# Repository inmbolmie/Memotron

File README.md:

# Memotron 256

__Retro-inspired DIY 256KB memory expansion for the Amstrad CPC 464 computers__

## Introduction

This is a clone of an original 1986 DK'Tronics 64/256KB memory expansion that is plugged into the expansion port of the CPC 464 computer. It is made as period-correct as possible regarding components and mechanical design, and at the same time it is possible to easily manufacture it at home as it uses only through-hole components.

If you have looked for these expansions you will know that they are quite hard to find and relatively expensive, especially for the 256KB variant.

If you like it or if you have any questions, you can drop me a message to my email __inmbolmie [AT] gmail [DOT] com__

## Design

The Memotron 256 has more or less the same board layout as the DK'Tronics 64/256KB memory expansion. I have changed the layout of the edge connectors though to make it easier to manufacture at the expense of taking a little more space on the desk, as the connectors are installed on the plane of the PCB and not perpendicular to it like in the original expansion.

So in the original expansion the PCB is in vertical position when plugged into the computer, while on the Memotron the PCB is placed horizontally. It will take more space but the designed 3D-printed case will provide adequate support for it.

Here you can see the Memotron next to the original DK'Tronics expansion PCB:

The board has an expansion edge connector like the original version where you can plug additional hardware, like disk drives, more expansions, etc.

## Compatibility

The expansion will operate exactly the same as the original. It has been tested on a CPC 464 computer adding to the expansion a Zaxxon DDI-1 disk controller and drive emulator

This is a screenshot of how the extra memory is seen on the Amstrad Diagnostics V1.3A application https://github.com/llopis/amstrad-diagnostics

It has been successfully used with games designed to make use of the 128KB of the CPC 6128, as well as some games and apps that will make use of the full 256KB (like Chibiakumas episode 2 https://www.chibiakumas.com/ep2/), and on CP/M 2.2

The expansion when plugged into a CPC 464 will have its memory mapped to banks 00-03 and you will have a total of 320KB of memory available.

The expansion can be configured with the jumpers also as a 64KB expansion, but this doesn't make much sense as the required memory ICs will cost more or less the same for getting 64KB or 256KB.

The Memotron can be used as a silicon disk connecting the jumper labelled as "Silicon disk enable". What this jumper really does is to change the RAM bank mappings from 00-03 to 04-07 so that you can plug two expansions at the same time for a total of 512KB of extra memory. Like in the original to really use it as a silicon disk you will need external roms not included.

Of course there are a lot of other memory expansions for the CPC made with modern components and going up to 4MB in size, that will be more convenient to use than this one. The point of this project though is being as period-correct as possible (no FPGA rubbish and so ;-) and to be possible to manufacture it at home.

## CPC 6128

Regarding the CPC 6128, the expansion seem to work on BASIC and games (Chibiakumas 2 will work and use the whole 256KB), but doesn't work on CP/M plus, so it is not really 100% compatible with the 6128. DK'Tronics had back in the day a specific version of these expansions for the 6128.

The expansion case feet are removable so contrary to the original one the Memotron will physically fit the 6128 without raising the computer.

When plugged into a CPC 6128, the expansion will have its memory mapped to banks 01-04 and you will have a total of 384KB of memory available.

## Board

There is not much to say about the board as it is the same general layout as the original. I provide all the Kicad designs for the project, as well as a ZIP file containing the gerbers needed to manufacture the board on your favourite online fabricator.

When using the services of a PCB fabricator I recommend manufacturing them with gold fingers and chamfered edge connector. Although that will increase the PCB cost substantially, it will improve the quality of the connection and make it more reliable even than that of the original expansions.

To configure the board as 256KB you will place two jumpers HORIZONTALLY as seen on the picture connecting JP1 to JP2. To configure the board as 64KB you will place only the JP2 jumper VERTICALLY.

### BOM

* One 2x25-pin 2,54mm pitch 90-degree bent edge connector
* 2x74LS157
* 1x74LS74
* 1x74LS153
* 1x74LS174
* 1x74LS27
* 1x74LS11
* 1xPAL16L8 or compatible
* 8xD41256C-15 256Kbit RAM or equivalent
* Pins and jumpers
* 3x680 ohm resistors
* 1x1N4148 diode
* 2xBF241 NPN transistors or equivalent
* 16x100nF ceramic capacitors
* 1x82nF ceramic capacitor (the value is critical and this and/or the value of the R3 resistor may need adjustment)
* Optionally, sockets for all the ICs. The original expansion only had sockets for the eight RAM chips

## 3D-printed enclosure

I provide the STL files for the 3D-printed enclosure that can be printed in four parts (top, bottom, feet and panel). There is a version of the top piece with and without the hole for the name plate.

You will need four M3x12mm and two M3x5mm tapered head screws for assembly.

The case is quite sturdy even printed in PLA and will take typically like 7 hours to print.

### PLD

Regarding the PLD that's on the board, the original expansion uses a vintage PAL16L8 ic that nowadays is pretty deprecated. You can get a vintage unprogrammed piece or use a modern ATF16V8B in its place. It will have to be programmed with a proper PLD programmer from a JED source file. I still don't have my own JED file but you can find one that is compatible with the original memory expansion (tagged as "Datel 64k memory expansion") on this site: https://wiki.pldarchive.co.uk

_"DK'Tronics" and "Datel" are registered trademarks.
All the trademarks are used nominatively to indicate compatibility, and do not indicate affiliation to or endorsement by the trademark owners._

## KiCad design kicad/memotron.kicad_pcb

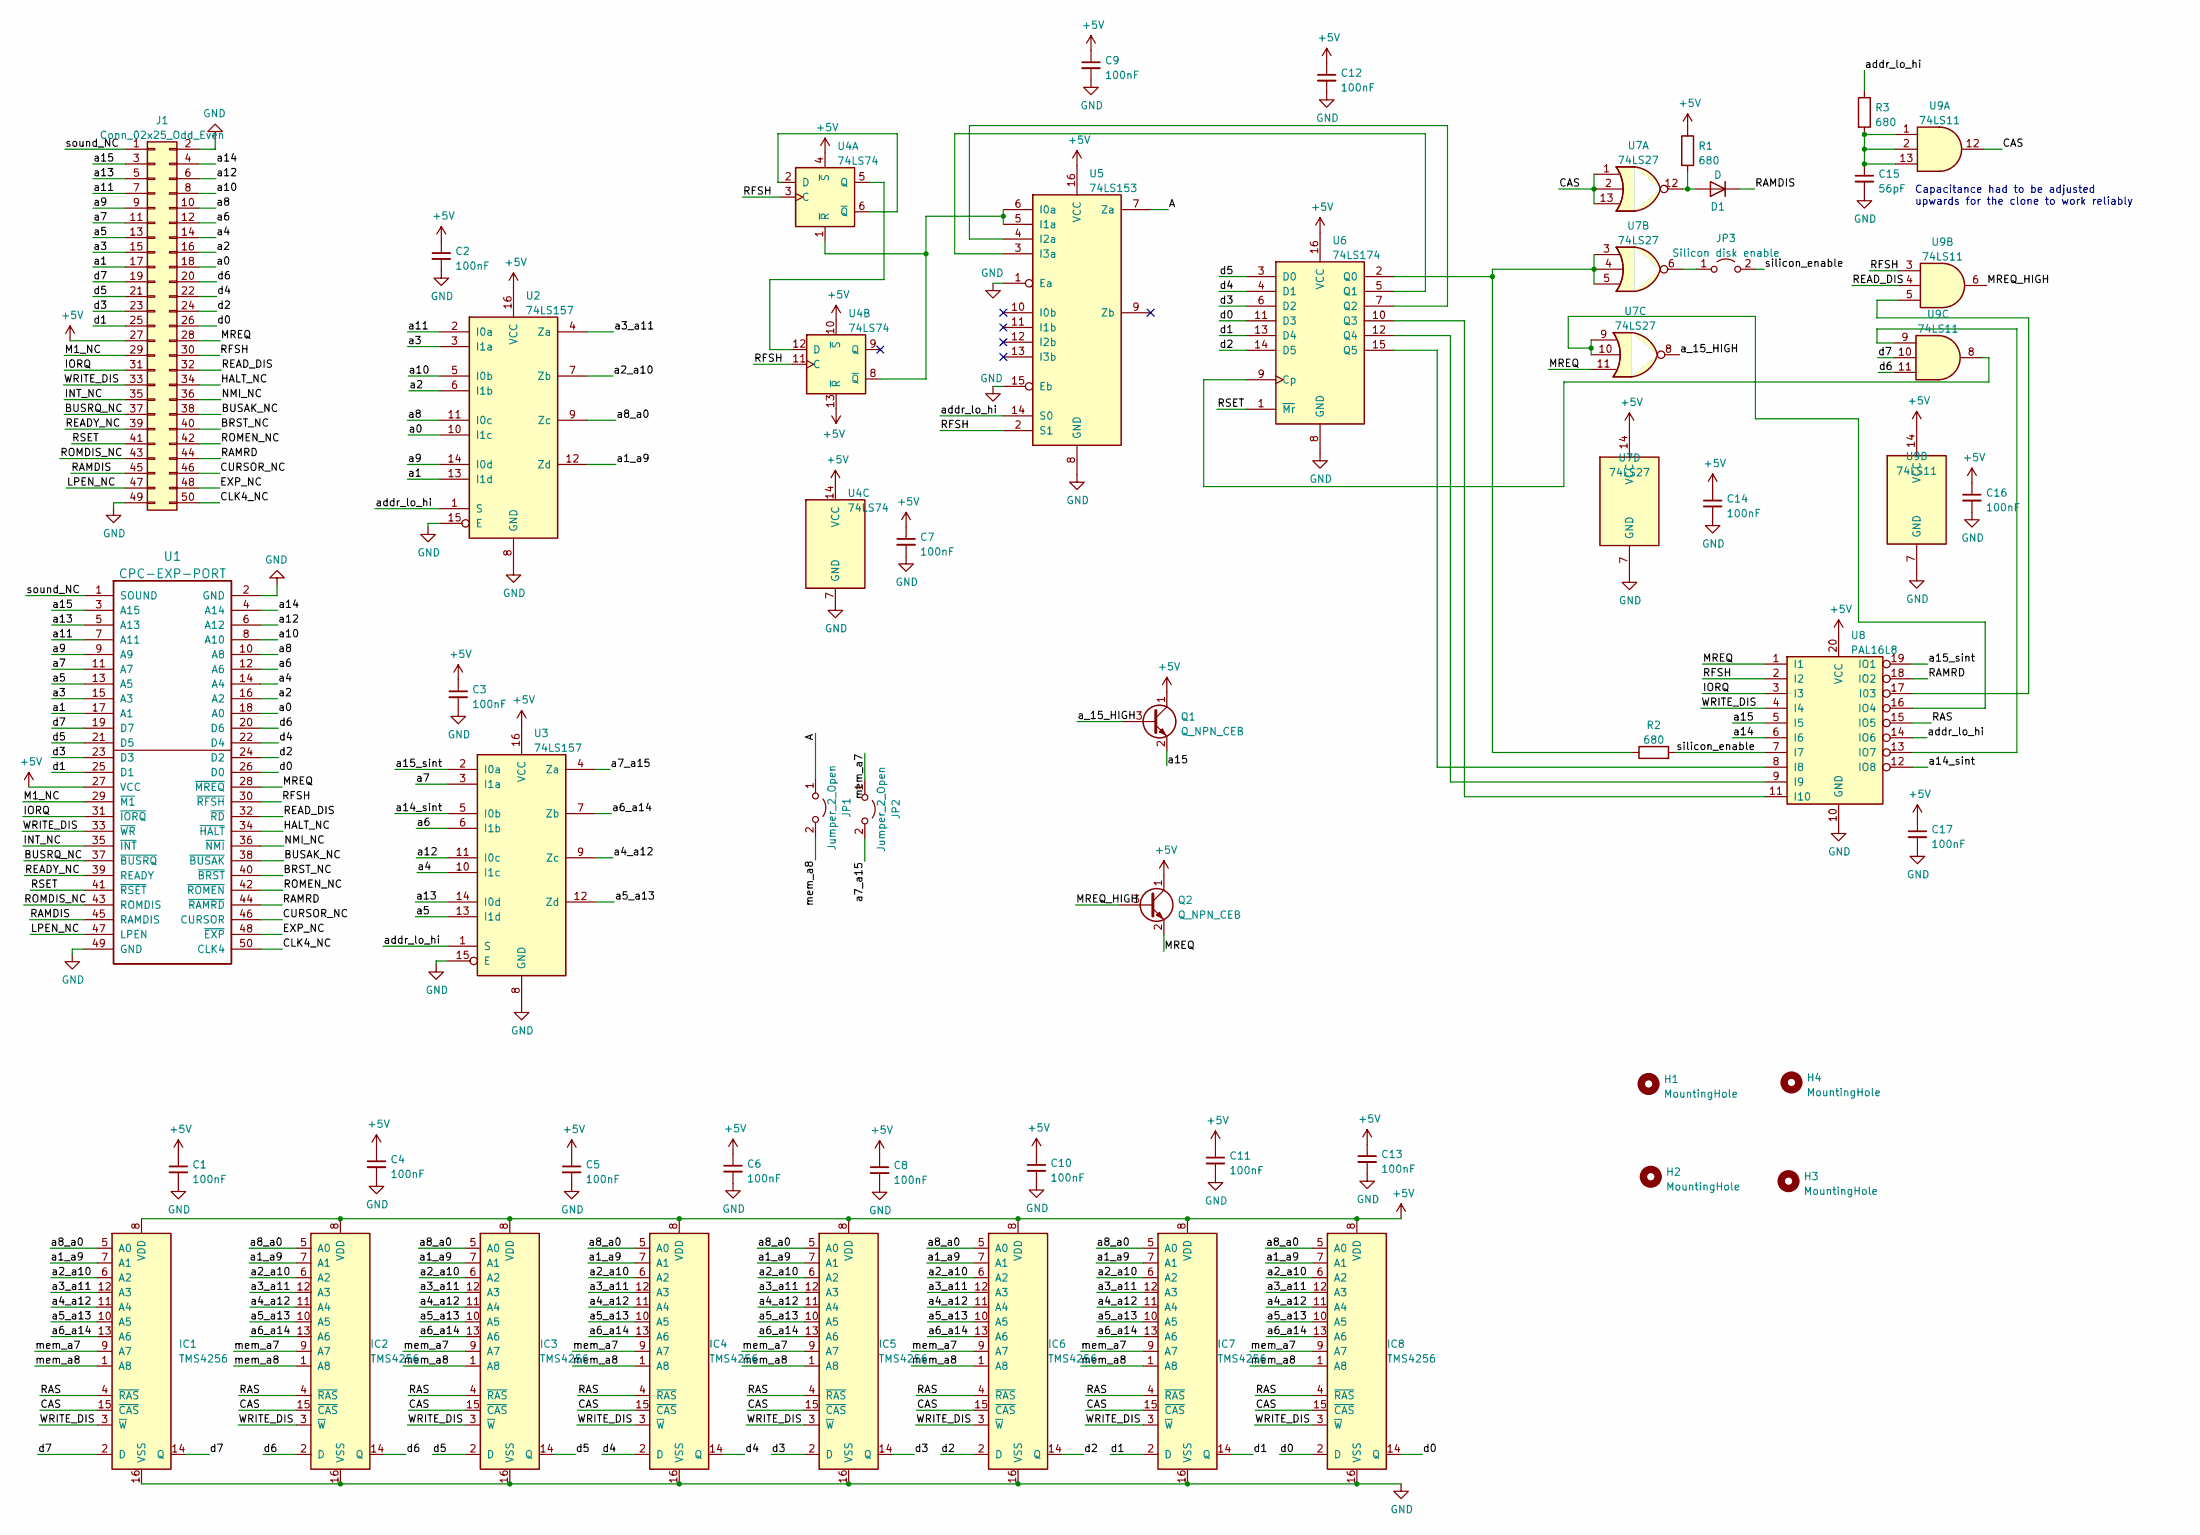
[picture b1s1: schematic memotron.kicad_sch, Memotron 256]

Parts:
C1, C2, C3, C4, C5, C6, C7, C8, C9, C10, C11, C12, C13, C14, C16, C17: 100nF; C_Disc_D6.0mm_W2.5mm_P5.00mm
C15: 56pF; C_Disc_D6.0mm_W2.5mm_P5.00mm
D1: D; D_A-405_P10.16mm_Horizontal
H1, H2, H3, H4: MountingHole; MountingHole_3.2mm_M3_DIN965
IC1, IC2, IC3, IC4, IC5, IC6, IC7, IC8: TMS4256; DIP-16_W7.62mm
J1: Conn_02x25_Odd_Even; PinHeader_2x25_P2.54mm_Horizontal
JP1, JP2: Jumper_2_Open; PinHeader_1x02_P2.54mm_Vertical
JP3: Silicon disk enable; PinHeader_1x02_P2.54mm_Vertical
Q1, Q2: Q_NPN_CEB; TO-92
R1, R2, R3: 680; R_Axial_DIN0309_L9.0mm_D3.2mm_P15.24mm_Horizontal
U1: CPC-EXP-PORT; edge_CPC_25x2
U2, U3: 74LS157; DIP-16_W7.62mm
U4: 74LS74; DIP-14_W7.62mm
U5: 74LS153; DIP-16_W7.62mm
U6: 74LS174; DIP-16_W7.62mm
U7: 74LS27; DIP-14_W7.62mm
U8: PAL16L8; DIP-20_W7.62mm
U9: 74LS11; DIP-14_W7.62mm

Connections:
+5V: C1.1, C2.1, C3.1, C4.1, C5.1, C6.1, C7.1, C8.1, C9.1, C10.1, C11.1, C12.1, C13.1, C14.1, C16.1, C17.1, IC1.8 (VDD), IC2.8 (VDD), IC3.8 (VDD), IC4.8 (VDD), IC5.8 (VDD), IC6.8 (VDD), IC7.8 (VDD), IC8.8 (VDD), J1.27, Q1.1 (C), Q2.1 (C), R1.1, U1.27 (VCC), U2.16 (VCC), U3.16 (VCC), U4.4 (~S), U4.10 (~S), U4.13 (~R), U4.14 (VCC), U5.16 (VCC), U6.16 (VCC), U7.14 (VCC), U8.20 (VCC), U9.14 (VCC)
/A: JP1.1 (A), U5.7 (Za)
/BRST_NC: J1.40, U1.40 (~BRST)
/BUSAK_NC: J1.38, U1.38 (~BUSAK)
/BUSRQ_NC: J1.37, U1.37 (~BUSRQ)
/CAS: IC1.15 (~CAS), IC2.15 (~CAS), IC3.15 (~CAS), IC4.15 (~CAS), IC5.15 (~CAS), IC6.15 (~CAS), IC7.15 (~CAS), IC8.15 (~CAS), U7.1, U7.2, U7.13, U9.12
/CLK4_NC: J1.50, U1.50 (CLK4)
/CURSOR_NC: J1.46, U1.46 (CURSOR)
/EXP_NC: J1.48, U1.48 (~EXP)
/HALT_NC: J1.34, U1.34 (~HALT)
/INT_NC: J1.35, U1.35 (~INT)
/IORQ: J1.31, U1.31 (~IORQ), U8.3 (I3)
/LPEN_NC: J1.47, U1.47 (LPEN)
/M1_NC: J1.29, U1.29 (~M1)
/MREQ: J1.28, Q2.2 (E), U1.28 (~MREQ), U7.11, U8.1 (I1)
/MREQ_HIGH: Q2.3 (B), U9.6
/NMI_NC: J1.36, U1.36 (~NMI)
/RAMDIS: D1.1 (K), J1.45, U1.45 (RAMDIS)
/RAMRD: J1.44, U1.44 (~RAMRD), U8.18 (IO2)
/RAS: IC1.4 (~RAS), IC2.4 (~RAS), IC3.4 (~RAS), IC4.4 (~RAS), IC5.4 (~RAS), IC6.4 (~RAS), IC7.4 (~RAS), IC8.4 (~RAS), U8.15 (IO5)
/READY_NC: J1.39, U1.39 (READY)
/READ_DIS: J1.32, U1.32 (~RD), U9.4
/RFSH: J1.30, U1.30 (~RFSH), U4.3 (C), U4.11 (C), U5.2 (S1), U8.2 (I2), U9.3
/ROMDIS_NC: J1.43, U1.43 (ROMDIS)
/ROMEN_NC: J1.42, U1.42 (~ROMEN)
/RSET: J1.41, U1.41 (~RSET), U6.1 (~Mr)
/WRITE_DIS: IC1.3 (~W), IC2.3 (~W), IC3.3 (~W), IC4.3 (~W), IC5.3 (~W), IC6.3 (~W), IC7.3 (~W), IC8.3 (~W), J1.33, U1.33 (~WR), U8.4 (I4)
/a0: J1.18, U1.18 (A0), U2.10 (I1c)
/a1: J1.17, U1.17 (A1), U2.13 (I1d)
/a1_a9: IC1.7 (A1), IC2.7 (A1), IC3.7 (A1), IC4.7 (A1), IC5.7 (A1), IC6.7 (A1), IC7.7 (A1), IC8.7 (A1), U2.12 (Zd)
/a2: J1.16, U1.16 (A2), U2.6 (I1b)
/a2_a10: IC1.6 (A2), IC2.6 (A2), IC3.6 (A2), IC4.6 (A2), IC5.6 (A2), IC6.6 (A2), IC7.6 (A2), IC8.6 (A2), U2.7 (Zb)
/a3: J1.15, U1.15 (A3), U2.3 (I1a)
/a3_a11: IC1.12 (A3), IC2.12 (A3), IC3.12 (A3), IC4.12 (A3), IC5.12 (A3), IC6.12 (A3), IC7.12 (A3), IC8.12 (A3), U2.4 (Za)
/a4: J1.14, U1.14 (A4), U3.10 (I1c)
/a4_a12: IC1.11 (A4), IC2.11 (A4), IC3.11 (A4), IC4.11 (A4), IC5.11 (A4), IC6.11 (A4), IC7.11 (A4), IC8.11 (A4), U3.9 (Zc)
/a5: J1.13, U1.13 (A5), U3.13 (I1d)
/a5_a13: IC1.10 (A5), IC2.10 (A5), IC3.10 (A5), IC4.10 (A5), IC5.10 (A5), IC6.10 (A5), IC7.10 (A5), IC8.10 (A5), U3.12 (Zd)
/a6: J1.12, U1.12 (A6), U3.6 (I1b)
/a6_a14: IC1.13 (A6), IC2.13 (A6), IC3.13 (A6), IC4.13 (A6), IC5.13 (A6), IC6.13 (A6), IC7.13 (A6), IC8.13 (A6), U3.7 (Zb)
/a7: J1.11, U1.11 (A7), U3.3 (I1a)
/a7_a15: JP2.2 (B), U3.4 (Za)
/a8: J1.10, U1.10 (A8), U2.11 (I0c)
/a8_a0: IC1.5 (A0), IC2.5 (A0), IC3.5 (A0), IC4.5 (A0), IC5.5 (A0), IC6.5 (A0), IC7.5 (A0), IC8.5 (A0), U2.9 (Zc)
/a9: J1.9, U1.9 (A9), U2.14 (I0d)
/a10: J1.8, U1.8 (A10), U2.5 (I0b)
/a11: J1.7, U1.7 (A11), U2.2 (I0a)
/a12: J1.6, U1.6 (A12), U3.11 (I0c)
/a13: J1.5, U1.5 (A13), U3.14 (I0d)
/a14: J1.4, U1.4 (A14), U8.6 (I6)
/a14_sint: U3.5 (I0b), U8.12 (IO8)
/a15: J1.3, Q1.2 (E), U1.3 (A15), U8.5 (I5)
/a15_sint: U3.2 (I0a), U8.19 (IO1)
/a_15_HIGH: Q1.3 (B), U7.8
/addr_lo_hi: R3.1, U2.1 (S), U3.1 (S), U5.14 (S0), U8.14 (IO6)
/d0: IC8.2 (D), IC8.14 (Q), J1.26, U1.26 (D0), U6.11 (D3)
/d1: IC7.2 (D), IC7.14 (Q), J1.25, U1.25 (D1), U6.13 (D4)
/d2: IC6.2 (D), IC6.14 (Q), J1.24, U1.24 (D2), U6.14 (D5)
/d3: IC5.2 (D), IC5.14 (Q), J1.23, U1.23 (D3), U6.6 (D2)
/d4: IC4.2 (D), IC4.14 (Q), J1.22, U1.22 (D4), U6.4 (D1)
/d5: IC3.2 (D), IC3.14 (Q), J1.21, U1.21 (D5), U6.3 (D0)
/d6: IC2.2 (D), IC2.14 (Q), J1.20, U1.20 (D6), U9.11
/d7: IC1.2 (D), IC1.14 (Q), J1.19, U1.19 (D7), U9.10
/mem_a7: IC1.9 (A7), IC2.9 (A7), IC3.9 (A7), IC4.9 (A7), IC5.9 (A7), IC6.9 (A7), IC7.9 (A7), IC8.9 (A7), JP2.1 (A)
/mem_a8: IC1.1 (A8), IC2.1 (A8), IC3.1 (A8), IC4.1 (A8), IC5.1 (A8), IC6.1 (A8), IC7.1 (A8), IC8.1 (A8), JP1.2 (B)
/silicon_enable: JP3.2 (B), R2.2, U8.7 (I7)
/sound_NC: J1.1, U1.1 (SOUND)
GND: C1.2, C2.2, C3.2, C4.2, C5.2, C6.2, C7.2, C8.2, C9.2, C10.2, C11.2, C12.2, C13.2, C14.2, C15.2, C16.2, C17.2, IC1.16 (VSS), IC2.16 (VSS), IC3.16 (VSS), IC4.16 (VSS), IC5.16 (VSS), IC6.16 (VSS), IC7.16 (VSS), IC8.16 (VSS), J1.2, J1.49, U1.2 (GND), U1.49 (GND), U2.8 (GND), U2.15 (E), U3.8 (GND), U3.15 (E), U4.7 (GND), U5.1 (Ea), U5.8 (GND), U5.15 (Eb), U6.8 (GND), U7.7 (GND), U8.10 (GND), U9.7 (GND)
unnamed: C15.1, R3.2, U9.1, U9.2, U9.13
unnamed: D1.2 (A), R1.2, U7.12
unnamed: JP3.1 (A), U7.6
unnamed: R2.1, U6.2 (Q0), U7.3, U7.4, U7.5
unnamed: U4.1 (~R), U4.8 (~Q), U5.5 (I1a), U5.6 (I0a)
unnamed: U4.2 (D), U4.6 (~Q)
unnamed: U4.5 (Q), U4.12 (D)
unnamed: U5.3 (I3a), U6.5 (Q1)
unnamed: U5.4 (I2a), U6.7 (Q2)
unnamed: U6.9 (Cp), U9.8
unnamed: U6.10 (Q3), U8.11 (I10)
unnamed: U6.12 (Q4), U8.9 (I9)
unnamed: U6.15 (Q5), U8.8 (I8)
unnamed: U7.9, U7.10, U8.16 (IO4)
unnamed: U8.13 (IO7), U9.9
unnamed: U8.17 (I03), U9.5

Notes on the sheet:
Capacitance had to be adjusted upwards for the clone to work reliably

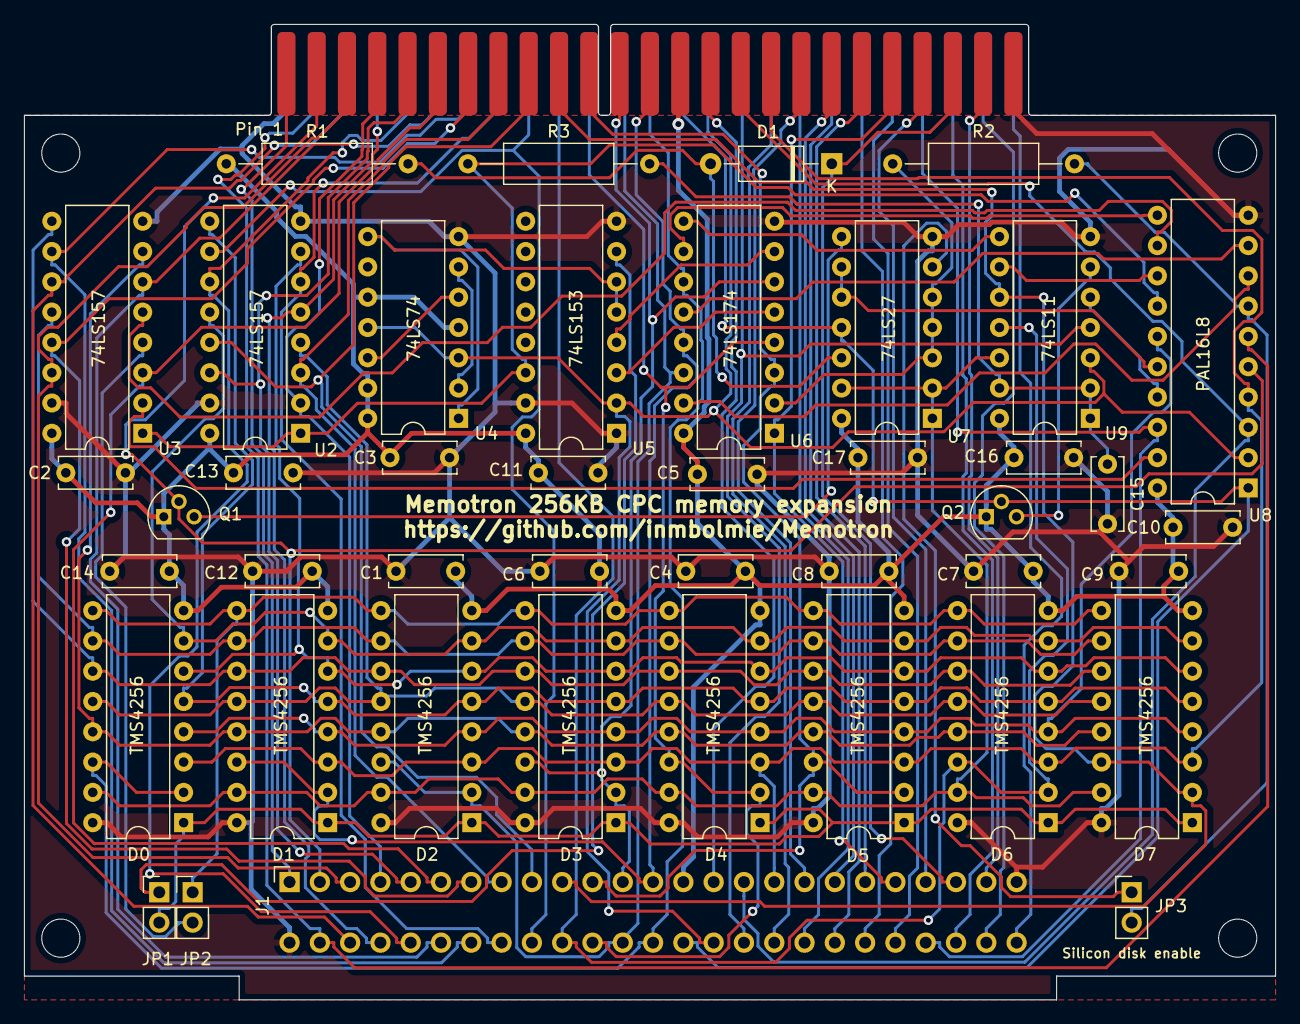
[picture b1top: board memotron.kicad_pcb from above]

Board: 2 copper layers, 104.9 x 81.8 mm, 48 parts (0 on the bottom side), 84 nets.
